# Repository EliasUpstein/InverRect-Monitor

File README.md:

# InverRect-Monitor

**Plataforma Ciberfísica de Simulación, Control HIL y Monitoreo SCADA para Electrónica de Potencia**

---

## 1. Visión y Propósito del Proyecto

**InverRect-Monitor** es una plataforma integral de ingeniería que fusiona la **simulación matemática de alta precisión** con el **control y monitoreo físico en tiempo real** de convertidores estáticos de potencia (rectificadores controlados y no controlados monofásicos y trifásicos, e inversores).

En el estudio y operación de la electrónica de potencia, existe a menudo una desconexión entre:
1. **Los modelos analíticos teóricos:** cálculo de potencias bajo condiciones no senoidales, descomposición en series de Fourier, impacto de armónicas en la red y comportamiento de cargas complejas ($R$, $L$, $C$).
2. **La implementación física de control:** detección precisa del cruce por cero de la red ($50\text{ Hz} / 60\text{ Hz}$), sincronización de microsegundos para el disparo de compuertas (SCR / TRIAC) y aislamiento galvánico de alta tensión.

**InverRect-Monitor** resuelve esta brecha creando un entorno tipo **Hardware-in-the-Loop (HIL) y SCADA**:
* Permite al usuario **analizar, simular y descomponer armónicamente** 12 topologías de convertidores bajo el estándar internacional **IEEE 1459**.
* Permite actuar como **consola SCADA de control remoto**, enviando el ángulo de disparo ($\alpha$) en tiempo real vía **Wi-Fi / UDP** hacia un microcontrolador **ESP32** dedicado al control físico de potencia, garantizando sincronismo estricto e inmunidad a retardos de software.

---

## 2. Arquitectura Global del Sistema Ciberfísico

El sistema opera mediante una división estricta entre la **estación de supervisión de alto nivel (PC)** y el **nodo de control de potencia en tiempo real (ESP32)**:

```
┌─────────────────────────────────────────────────────────────────────────────┐
│                      ESTACIÓN DE SUPERVISIÓN (PC)                           │
│                                                                             │
│   ┌─────────────────────┐   ┌────────────────────────┐   ┌──────────────┐   │
│   │     calculos.py     │◄─►│      interfaz.py       │◄─►│   main.py    │   │
│   │ (NumPy/IEEE 1459/SF)│   │(Tkinter/Matplotlib/UDP)│   │ (Controller) │   │
│   └─────────────────────┘   └───────────┬────────────┘   └──────────────┘   │
└─────────────────────────────────────────┼───────────────────────────────────┘
                                          │ Datagramas UDP ("ALFA:xx.x")
                                          │ Wi-Fi 802.11 (Puerto 8888)
                                          ▼
┌─────────────────────────────────────────────────────────────────────────────┐
│                   NODO DE CONTROL EN TIEMPO REAL (ESP32)                    │
│                                                                             │
│   ┌─────────────────────────────────────┐   ┌───────────────────────────┐   │
│   │               CORE 0                │   │          CORE 1           │   │
│   │   • Tarea FreeRTOS Comunicaciones   │   │   • ISR Cruce por Cero    │   │
│   │   • Servidor UDP & ArduinoOTA       │◄─►│   • Hardware Timer (1 MHz)│   │
│   │   • Sincronización atómica (MUX)    │   │   • Pulso de compuerta    │   │
│   └─────────────────────────────────────┘   └─────────────┬─────────────┘   │
└───────────────────────────────────────────────────────────┼─────────────────┘
                                                            │
                      ┌─────────────────────────────────────┴─────────────┐
                      ▼                                                   ▼
            ┌───────────────────┐                               ┌───────────────────┐
            │  ENTRADA DIGITAL  │                               │  SALIDA DIGITAL   │
            │  GPIO 18 (ZC)     │                               │  GPIO 19 (Gate)   │
            └─────────▲─────────┘                               └─────────┬─────────┘
                      │                                                   │
                      │ Pulso 50 Hz                                       │ Pulso 50 µs
            ┌─────────┴─────────┐                               ┌─────────┴─────────┐
            │ Optoacoplador ZC  │                               │ Driver Opto-TRIAC │
            │      (PC817)      │                               │     (MOC3021)     │
            └─────────▲─────────┘                               └─────────┬─────────┘
                      │                                                   │
     Red Eléctrica ───┴───────────────── Circuito de Potencia ────────────┴──► Carga
     (220V CA / 50 Hz)                   (Tiristores SCR / TRIAC)              (R-L-C)
```

---

## 3. Estructura del Monorepo y Documentación Detallada

El proyecto está organizado de forma modular. Cada subsistema cuenta con su documentación técnica exhaustiva:

```
InverRect-Monitor/
├── pc_software/             # Software de PC: Analizador matemático y panel SCADA
│   ├── calculos.py          # Modelo: Síntesis de ondas, Fourier y cálculo IEEE 1459
│   ├── interfaz.py          # Vista: Interfaz gráfica industrial Tkinter + cliente UDP
│   ├── main.py              # Controlador: Ciclo de vida de la aplicación
│   └── README.md            # 📖 Documentación técnica completa del software de PC
│
├── esp32_firmware/          # Firmwares embebidos para el microcontrolador ESP32 (Arduino IDE)
│   ├── rectificador/        # Sketch del Rectificador Monofásico (ZCD, SCR, ADC, UDP, OTA)
│   │   └── rectificador.ino
│   ├── inversor/            # Sketch modular del Inversor Monofásico (MCPWM 50Hz, Dead-Time, ADC1, UDP, OTA)
│   │   ├── inversor.ino
│   │   ├── config.h
│   │   ├── inverter_mcpwm.h / .cpp
│   │   ├── acquisition.h / .cpp
│   │   └── comms.h / .cpp
│   └── README.md            # 📖 Documentación técnica de hardware, pines, OTA y prueba en osciloscopio
│
├── assets/                  # Diagramas y capturas de pantalla
├── .gitignore               # Filtros de Git para entornos Python y compilaciones C++
└── README.md                # 📖 Visión general del proyecto (este archivo)
```

* 👉 **[Documentación del Software de PC (`pc_software/README.md`)](pc_software/README.md):** Contiene la explicación de los cálculos matemáticos (Fourier, impedancias complejas $R$-$X$, formulación IEEE 1459), descripción de las 12 señales simuladas, guía de la interfaz gráfica y configuración del cliente UDP.
* 👉 **[Documentación del Firmware ESP32 (`esp32_firmware/README.md`)](esp32_firmware/README.md):** Contiene el diagrama de conexionado eléctrico, pinout (GPIO 18 y 19), configuración de FreeRTOS, actualización inalámbrica vía ArduinoOTA y sincronización atómica con spinlocks.

---

## 4. Características Principales

### 🔬 Análisis Matemático y Procesamiento de Señales
* **Correlación Trigonométrica de Fourier (sin FFT):** Cálculo exacto de coeficientes ($a_n, b_n$) mediante integración numérica en el dominio temporal discreto. Evita problemas de *picket-fence* y dispersión espectral (*spectral leakage*) propios de la FFT en señales no periódicas o truncadas.
* **Norma IEEE 1459:** Computa potencia activa ($P$), aparente ($S$), reactiva fundamental ($Q$), distorsión armónica ($D$), factor de potencia ($FP = P/S$) y distorsión armónica total de tensión y corriente ($\text{THD}_V, \text{THD}_I$).
* **Modelado de Impedancias Complejas:** Respuesta dinámica de corriente considerando armónica fundamental y armónicas superiores ($X_n = nX$ para cargas inductivas y $X_n = X/n$ para capacitivas).
* **Biblioteca de 12 Topologías:** Senoidal pura, cuadrada, cuasi-cuadrada, rectificadores monofásicos y trifásicos (media onda y onda completa, controlados y no controlados) y simulación de entrada analógica ADC con ruido gaussiano.

### 🖥️ Interfaz Gráfica SCADA de Alta Legibilidad
* **Diseño Industrial:** Optimizado para pantallas industriales y monitores con escalado DPI (hasta 1080p con 125% DPI scaling).
* **Visualización en Dos Subplots:**
  * Dominio del tiempo: tensión y corriente superpuestas en 2 ciclos con marcación del ángulo $\alpha$.
  * Dominio de la frecuencia: espectro de barras lado a lado de armónicas RMS de tensión y corriente.
* **Cursores Interactivos:** Inspección de valores puntuales al hacer clic sobre cualquier punto de las curvas.
* **Modo en Tiempo Real:** Bucle de simulación y refresco continuo configurable en segundos.

### ⚡ Control de Hardware Físico en Tiempo Real
* **Microsegundos de Precisión:** El ESP32 ejecuta la sincronización de cruce por cero y el temporizador de hardware en el Core 1 con código en `IRAM`, asegurando un disparo libre de jitter. Incorpora un filtro de ventana de supresión de $7000\,\mu\text{s}$ contra transitorios y rebotes en la red de 50 Hz.
* **Enlace Inalámbrico Bidireccional con Handshake (ACK/NACK):** El operador configura la IP en la PC y despacha el comando `"ALFA:xx.x"`. La aplicación verifica activamente la conexión aguardando el paquete de confirmación `"ACK:ALFA:xx.x"` emitido por el ESP32, alertando con precisión si el microcontrolador está apagado o la IP es inalcanzable.
* **Protección de Seguridad Industrial y Monotonicidad:** Compensación continua de retardo de optoacoplador que previene saltos bruscos en bajas conducciones, y validación automática en la interfaz que restringe el ángulo estrictamente al rango seguro $0.0^\circ \le \alpha \le 180.0^\circ$.
* **Flasheo Inalámbrico (OTA):** Soporte para reprogramar el firmware del ESP32 a distancia mientras se encuentra instalado en el banco de pruebas.

---

## 5. Modos de Operación

El sistema puede utilizarse en tres modalidades operativas:

1. **Modo Simulación Pura (Educativo / Diseño):**
   * Se selecciona cualquiera de las topologías de convertidor (índices 0 a 10).
   * Se ajusta la amplitud de tensión, el ángulo de disparo teórico $\alpha$ y los valores de $R$ y $X$.
   * La aplicación reconstruye las ondas analíticas y calcula inmediatamente todos los parámetros de calidad de energía y el espectro armónico.
2. **Modo Hardware-in-the-Loop (HIL) y Control Remoto:**
   * La aplicación de PC se conecta al ESP32 ingresando su dirección IP en la sección de control de hardware.
   * Al modificar $\alpha$ y presionar **"Enviar Ángulo (α) al Hardware"**, el ESP32 actualiza instantáneamente el retardo de compuerta en el circuito de tiristores real.
   * Permite contrastar la respuesta teórica calculada en la PC contra las mediciones en osciloscopio tomadas sobre el convertidor físico.
3. **Modo Instrumentación / Telemetría ADC:**
   * Seleccionando la señal `11. Muestras ADC (Simuladas)`, el sistema evalúa señales analógicas adquiridas con componentes estocásticos de ruido.
   * Permite continuar despachando órdenes de hardware al ESP32 manteniendo independiente el análisis de la señal capturada.

---

## 6. Puesta en Marcha Rápida (Quickstart)

### Paso 1: Clonar el Repositorio
```bash
git clone https://github.com/EliasUpstein/InverRect-Monitor.git
cd InverRect-Monitor
```

### Paso 2: Configurar el Entorno Python
```bash
# Crear entorno virtual
python -m venv venv

# Activar entorno virtual
# En Windows:
venv\Scripts\activate
# En Linux/macOS:
source venv/bin/activate

# Instalar dependencias
pip install numpy matplotlib
```

### Paso 3: Ejecutar la Interfaz de PC
```bash
python pc_software/main.py
```

### Paso 4 (Opcional): Cargar el Firmware al ESP32
1. Abrir `esp32_firmware/rectificador/rectificador.ino` o `esp32_firmware/inversor/inversor.ino` en Arduino IDE (o PlatformIO).
2. Configurar `WIFI_SSID` y `WIFI_PASSWORD` en el sketch (para el inversor, en `esp32_firmware/inversor/config.h`).
3. Flashear el microcontrolador por primera vez vía USB y observar la IP en el Monitor Serie (115200 bps). Las siguientes actualizaciones pueden realizarse por **ArduinoOTA** (`esp32-rmmoc` o `esp32-inversor`).
4. Seleccionar el dispositivo (`Rectificador` o `Inversor`) e ingresar la IP en la interfaz gráfica de PC.

---

## 7. Referencias Normativas y Bibliográficas
* **IEEE Std 1459-2010:** *IEEE Standard Definitions for the Measurement of Electric Power Quantities Under Sinusoidal, Nonsinusoidal, Balanced, or Unbalanced Conditions*.
* **Mohan, Undeland, Robbins:** *Power Electronics: Converters, Applications, and Design*, John Wiley & Sons.
* **Rashid, Muhammad H.:** *Power Electronics Handbook*, Academic Press.
* **Espressif Systems:** *ESP32 Technical Reference Manual & FreeRTOS Architecture*.

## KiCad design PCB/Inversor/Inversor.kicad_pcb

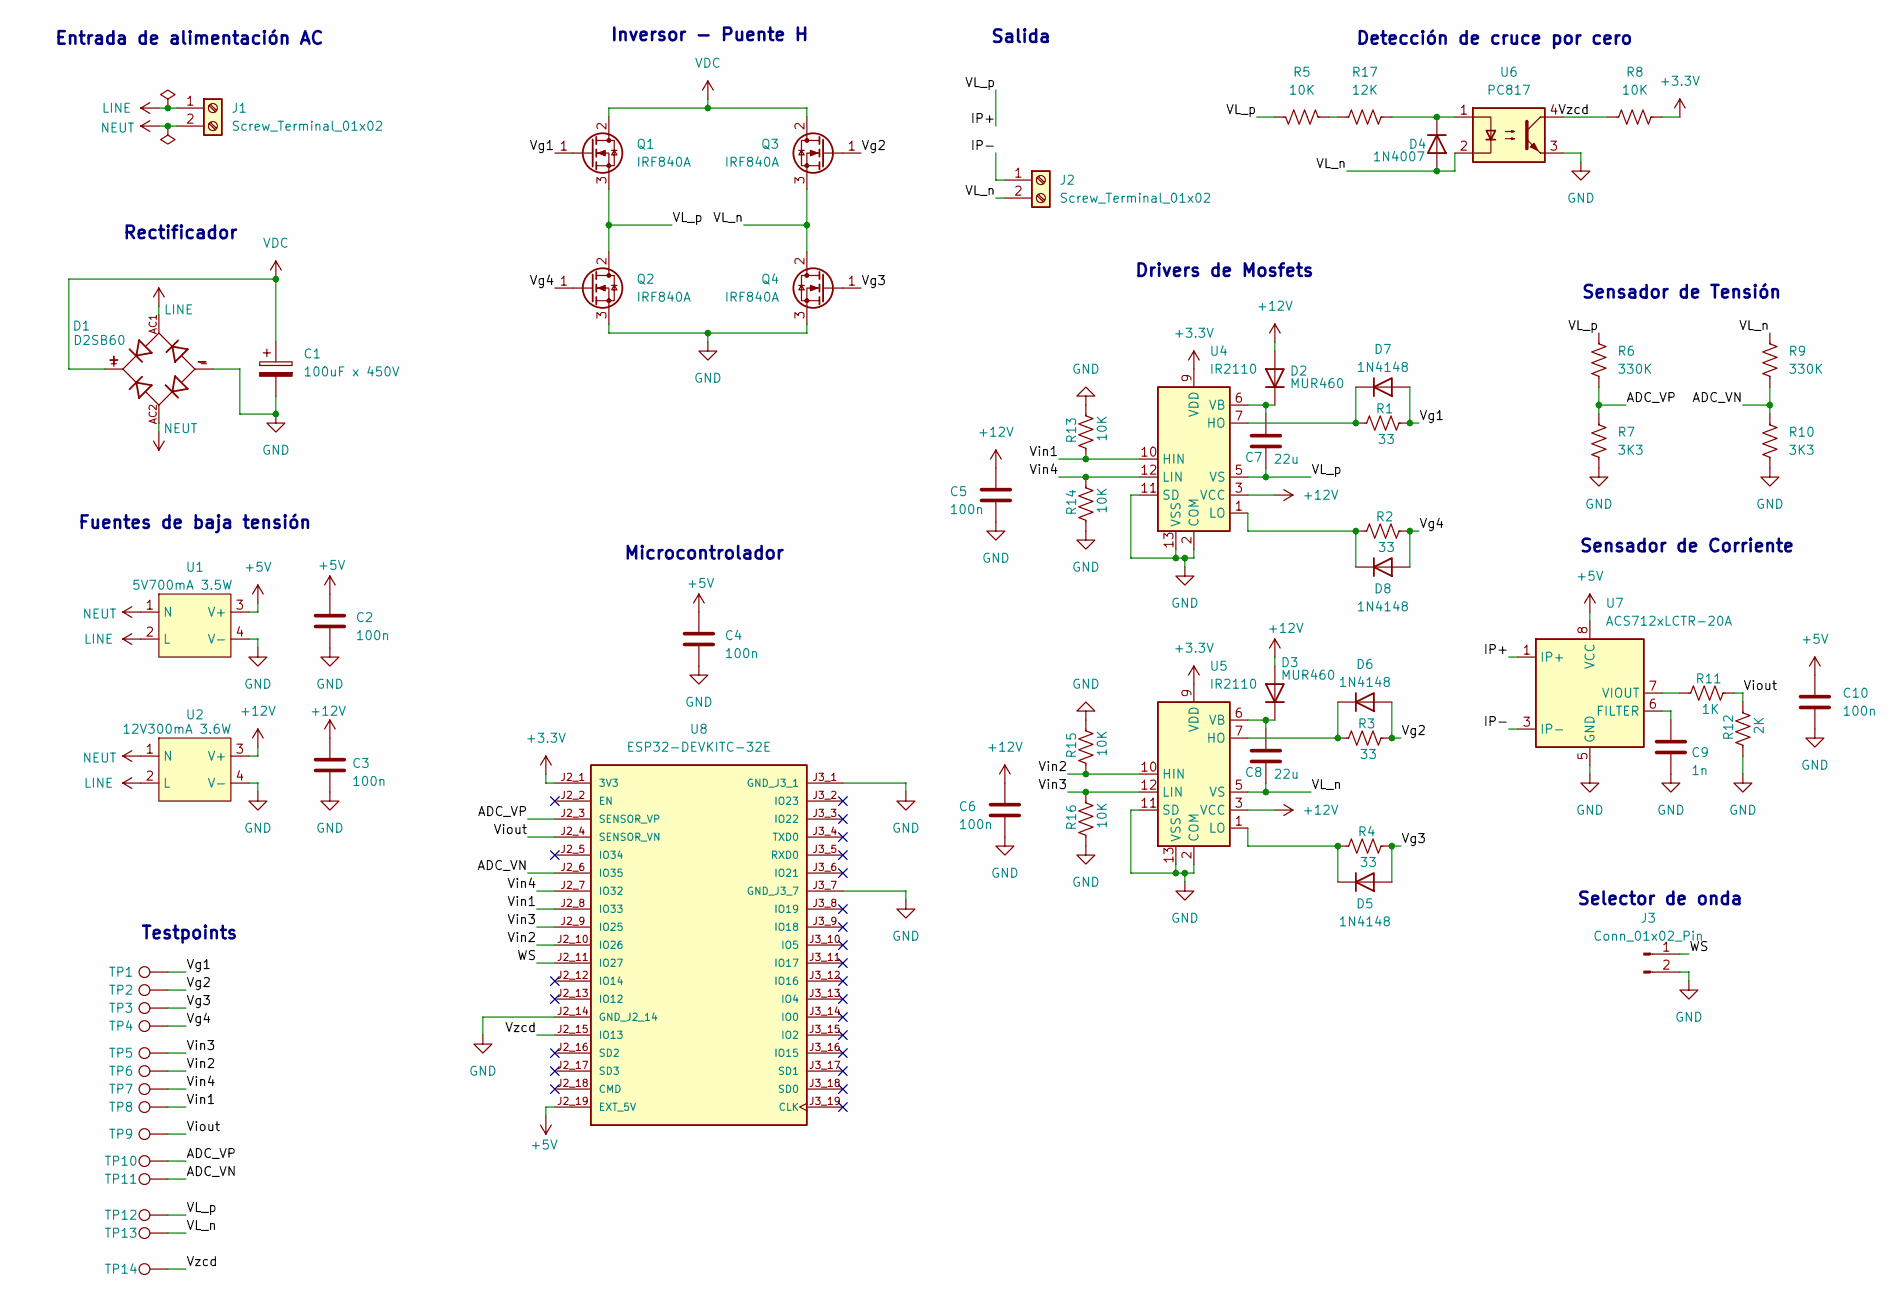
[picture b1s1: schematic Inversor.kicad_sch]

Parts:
C1: 100uF x 450V; CP_Radial_D18.0mm_P7.50mm
C2, C3, C4, C5, C6, C10: 100n; C_Disc_D4.3mm_W1.9mm_P5.00mm
C7: 22u; CP_Radial_D5.0mm_P2.00mm
C8: 22u; CP_Radial_D4.0mm_P2.00mm
C9: 1n; C_Disc_D4.3mm_W1.9mm_P5.00mm
D1: D2SB60; SIP350W100P500L2000H1400Q4; MPN D2SB60
D2, D3: MUR460; D_DO-41_SOD81_P10.16mm_Horizontal
D4: 1N4007; D_DO-41_SOD81_P10.16mm_Horizontal
D5, D6, D7, D8: 1N4148; D_DO-35_SOD27_P7.62mm_Horizontal
J1, J2: Screw_Terminal_01x02; TerminalBlock_Phoenix_MKDS-1,5-2-5.08_1x02_P5.08mm_Horizont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
J3: Conn_01x02_Pin; PinHeader_2x01_P2.54mm_Vertical
Q1, Q2, Q3, Q4: IRF840A; TO-220-3_Vertical
R1, R2, R3, R4: 33; R_Axial_DIN0309_L9.0mm_D3.2mm_P15.24mm_Horizontal
R5: 10K; R_Axial_DIN0414_L11.9mm_D4.5mm_P25.40mm_Horizontal
R6, R9: 330K; R_Axial_DIN0309_L9.0mm_D3.2mm_P15.24mm_Horizontal
R7, R10: 3K3; R_Axial_DIN0309_L9.0mm_D3.2mm_P15.24mm_Horizontal
R8, R13, R14, R15, R16: 10K; R_Axial_DIN0309_L9.0mm_D3.2mm_P15.24mm_Horizontal
R11: 1K; R_Axial_DIN0309_L9.0mm_D3.2mm_P15.24mm_Horizontal
R12: 2K; R_Axial_DIN0309_L9.0mm_D3.2mm_P15.24mm_Horizontal
R17: 12K; R_Axial_DIN0414_L11.9mm_D4.5mm_P25.40mm_Horizontal
TP1, TP2, TP3, TP4, TP5, TP6, TP7, TP8, TP9, TP10, TP11, TP12, TP13, TP14: TestPoint; PinHeader_1x01_P2.54mm_Vertical
U1: 5V700mA 3.5W; WX-DC12003
U2: 12V300mA 3.6W; WX-DC12003
U4, U5: IR2110; DIP-14_W7.62mm
U6: PC817; DIP-4_W7.62mm
U7: ACS712xLCTR-20A; SOIC-8_3.9x4.9mm_P1.27mm
U8: ESP32-DEVKITC-32E; MODULE_ESP32-DEVKITC-32E; MPN ESP32-DEVKITC-32E

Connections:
+3.3V: R8.2, U4.9 (VDD), U5.9 (VDD), U8.J2_1 (3V3)
+5V: C2.1, C4.1, C10.1, U1.3 (V+), U7.8 (VCC), U8.J2_19 (EXT_5V)
+12V: C3.1, C5.1, C6.1, D2.2 (A), D3.2 (A), U2.3 (V+), U4.3 (VCC), U5.3 (VCC)
/ADC_VN: R9.2, R10.1, TP11.1 (1_1), U8.J2_6 (IO35)
/ADC_VP: R6.2, R7.1, TP10.1 (1_1), U8.J2_3 (SENSOR_VP)
/IP+: C7.2, Q1.3 (S), Q2.2 (D), R5.2, R6.1, TP12.1 (1_1), U4.5 (VS), U7.1 (IP+), U7.2 (IP+)
/IP-: J2.1, U7.3 (IP-), U7.4 (IP-)
/VL_n: C8.2, D4.2 (A), J2.2, Q3.3 (S), Q4.2 (D), R9.1, TP13.1 (1_1), U5.5 (VS), U6.2
/Vg1: D7.2 (A), Q1.1 (G), R1.2, TP1.1 (1_1)
/Vg2: D6.2 (A), Q3.1 (G), R3.2, TP2.1 (1_1)
/Vg3: D5.2 (A), Q4.1 (G), R4.2, TP3.1 (1_1)
/Vg4: D8.2 (A), Q2.1 (G), R2.2, TP4.1 (1_1)
/Vin1: R13.1, TP8.1 (1_1), U4.10 (HIN), U8.J2_8 (IO33)
/Vin2: R15.1, TP6.1 (1_1), U5.10 (HIN), U8.J2_10 (IO26)
/Vin3: R16.2, TP5.1 (1_1), U5.12 (LIN), U8.J2_9 (IO25)
/Vin4: R14.2, TP7.1 (1_1), U4.12 (LIN), U8.J2_7 (IO32)
/Viout: R11.2, R12.2, TP9.1 (1_1), U8.J2_4 (SENSOR_VN)
/Vzcd: R8.1, TP14.1 (1_1), U6.4, U8.J2_15 (IO13)
/WS: J3.1, U8.J2_11 (IO27)
GND: C1.2, C2.2, C3.2, C4.2, C5.2, C6.2, C9.2, C10.2, D1.-, J3.2, Q2.3 (S), Q4.3 (S), R7.2, R10.2, R12.1, R13.2, R14.1, R15.2, R16.1, U1.4 (V-), U2.4 (V-), U4.2 (COM), U4.11 (SD), U4.13 (VSS), U5.2 (COM), U5.11 (SD), U5.13 (VSS), U6.3, U7.5 (GND), U8.J2_14 (GND_J2_14), U8.J3_1 (GND_J3_1), U8.J3_7 (GND_J3_7)
LINE: D1.AC1, J1.1, U1.2 (L), U2.2 (L)
NEUT: D1.AC2, J1.2, U1.1 (N), U2.1 (N)
unnamed: C7.1, D2.1 (K), U4.6 (VB)
unnamed: C8.1, D3.1 (K), U5.6 (VB)
unnamed: D4.1 (K), R17.2, U6.1
unnamed: D5.1 (K), R4.1, U5.1 (LO)
unnamed: D6.1 (K), R3.1, U5.7 (HO)
unnamed: D7.1 (K), R1.1, U4.7 (HO)
unnamed: D8.1 (K), R2.1, U4.1 (LO)
unnamed: R5.1, R17.1
unnamed: C9.1, U7.6 (FILTER)
unnamed: R11.1, U7.7 (VIOUT)
VDC: C1.1, D1.+, Q1.2 (D), Q3.2 (D)

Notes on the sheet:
Inversor - Puente H
Fuentes de baja tensión
Testpoints
Rectificador
Sensador de Tensión
Microcontrolador
Detección de cruce por cero
Entrada de alimentación AC
Selector de onda
Sensador de Corriente
Drivers de Mosfets
Salida

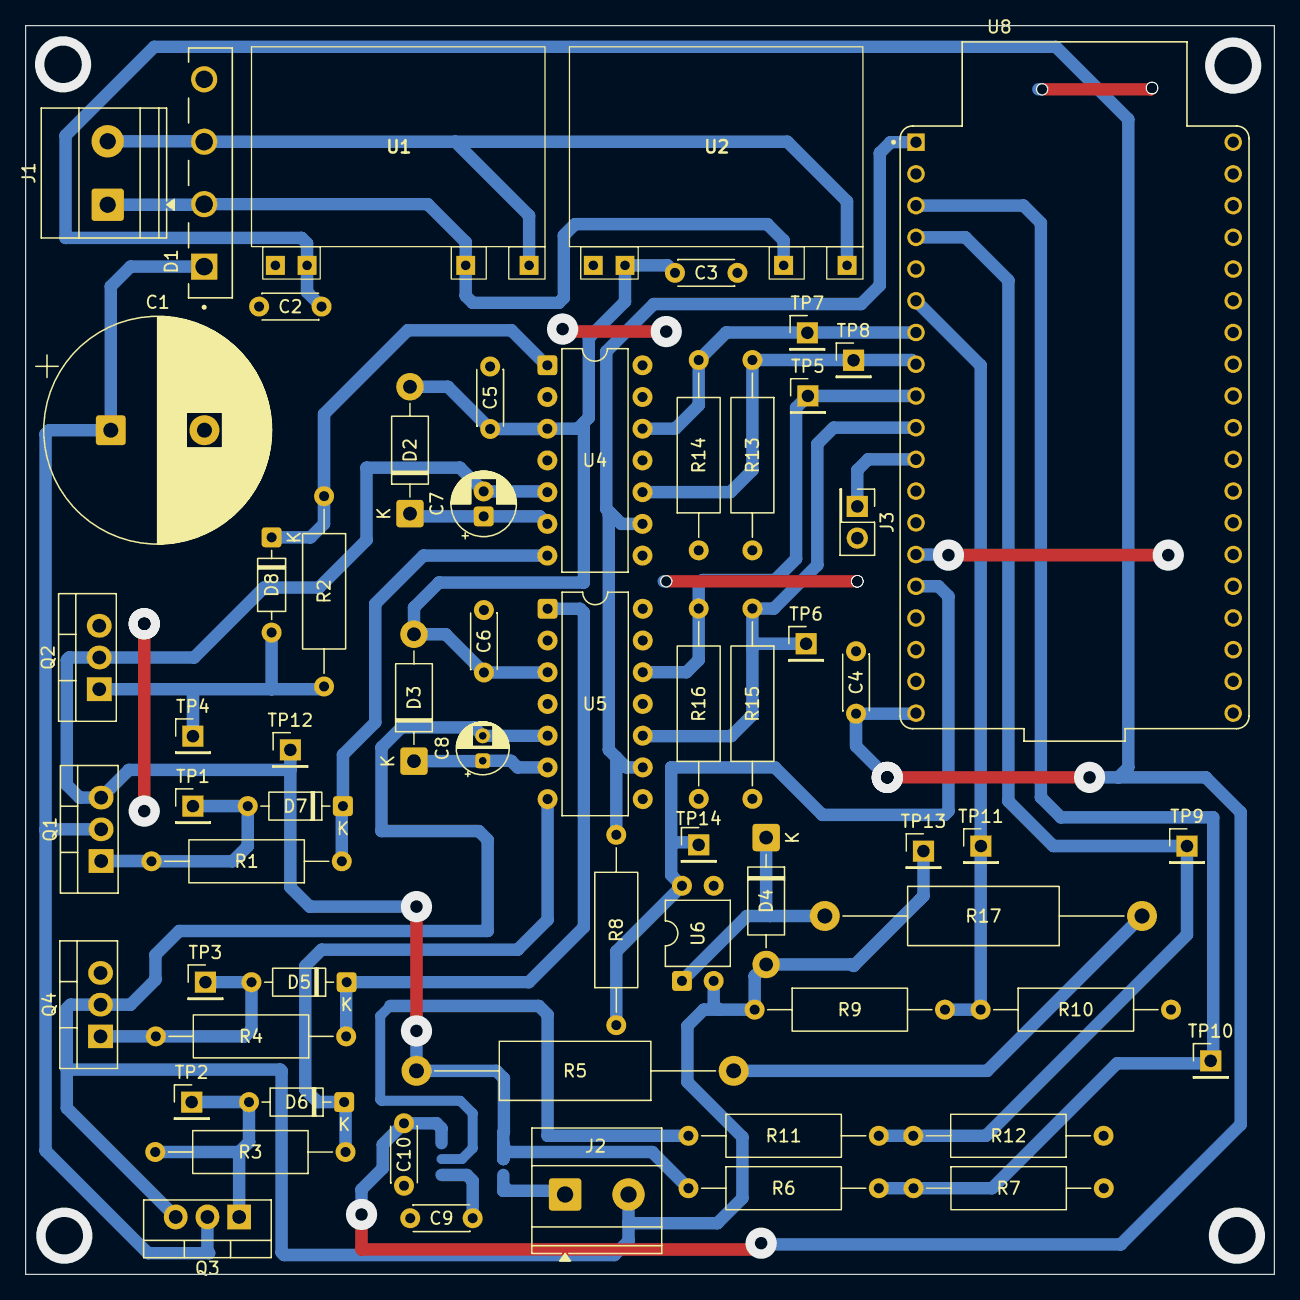
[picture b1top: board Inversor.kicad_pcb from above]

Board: 2 copper layers, 100.0 x 100.0 mm, 63 parts (1 on the bottom side), 33 nets.

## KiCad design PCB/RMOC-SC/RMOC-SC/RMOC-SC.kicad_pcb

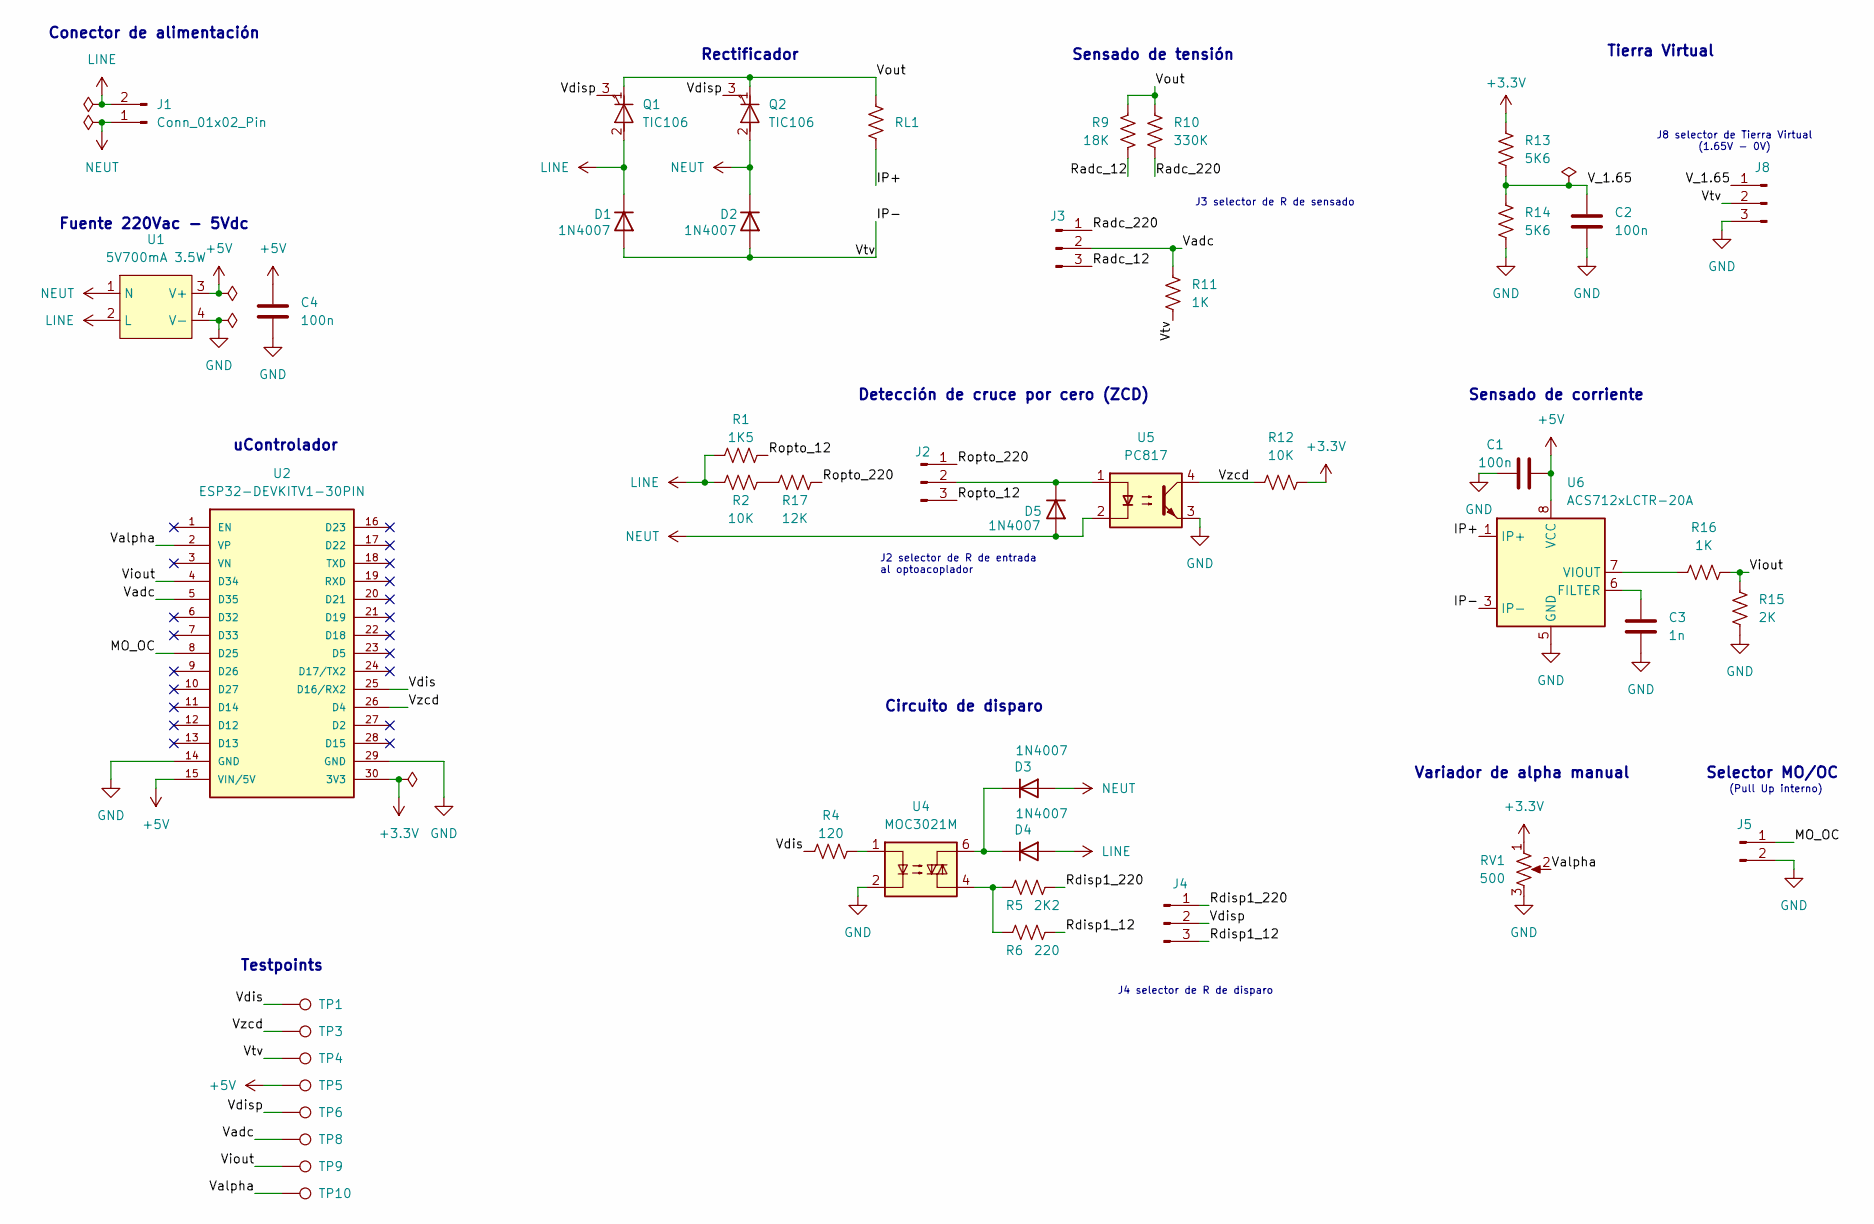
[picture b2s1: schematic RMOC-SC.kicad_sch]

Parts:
C1, C2, C4: 100n; C_Disc_D5.0mm_W2.5mm_P5.00mm
C3: 1n; C_Disc_D5.0mm_W2.5mm_P5.00mm
D1, D2, D3, D4, D5: 1N4007; D_DO-41_SOD81_P10.16mm_Horizontal
J1: Conn_01x02_Pin; Conn_220_tipo8
J2, J3, J4, J8: Conn_01x03_Pin; PinHeader_1x03_P2.54mm_Vertical
J5: Conn_01x02_Pin; PinHeader_1x02_P2.54mm_Vertical
Q1, Q2: TIC106; TO-220-3_Vertical
R1: 1K5; R_Axial_DIN0309_L9.0mm_D3.2mm_P12.70mm_Horizontal
R2: 10K; R_Axial_DIN0614_L14.3mm_D5.7mm_P20.32mm_Horizontal
R4: 120; R_Axial_DIN0309_L9.0mm_D3.2mm_P12.70mm_Horizontal
R5: 2K2; R_Axial_DIN0309_L9.0mm_D3.2mm_P12.70mm_Horizontal
R6: 220; R_Axial_DIN0309_L9.0mm_D3.2mm_P12.70mm_Horizontal
R9: 18K; R_Axial_DIN0309_L9.0mm_D3.2mm_P12.70mm_Horizontal
R10: 330K; R_Axial_DIN0309_L9.0mm_D3.2mm_P12.70mm_Horizontal
R11, R16: 1K; R_Axial_DIN0309_L9.0mm_D3.2mm_P12.70mm_Horizontal
R12: 10K; R_Axial_DIN0309_L9.0mm_D3.2mm_P12.70mm_Horizontal
R13, R14: 5K6; R_Axial_DIN0309_L9.0mm_D3.2mm_P12.70mm_Horizontal
R15: 2K; R_Axial_DIN0309_L9.0mm_D3.2mm_P12.70mm_Horizontal
R17: 12K; R_Axial_DIN0614_L14.3mm_D5.7mm_P20.32mm_Horizontal
RL1: R_US; Altech_AK100_1x02_P5.00mm
RV1: 500; Potentiometer_Piher_PC-16_Single_Horizontal
TP1, TP3, TP4, TP5, TP6, TP8, TP9, TP10: TestPoint; PinHeader_1x01_P2.54mm_Vertical
U1: 5V700mA 3.5W; WX-DC12003
U2: ESP32-DEVKITV1-30PIN; ESP32-DEVKIT-30PIN; PARTREV V4
U4: MOC3021M; DIP-6_W7.62mm_LongPads
U5: PC817; DIP-4_W7.62mm
U6: ACS712xLCTR-20A; SOIC-8_3.9x4.9mm_P1.27mm

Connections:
+3.3V: R12.2, R13.1, RV1.1, U2.30 (3V3)
+5V: C1.2, C4.1, TP5.1 (1_1), U1.3 (V+), U2.15 (VIN/5V), U6.8 (VCC)
/IP+: RL1.2, U6.1 (IP+), U6.2 (IP+)
/IP-: D1.2 (A), D2.2 (A), J8.2, R11.2, TP4.1 (1_1), U6.3 (IP-), U6.4 (IP-)
/MO_OC: J5.1, U2.8 (D25)
/Radc_12: J3.3, R9.2
/Radc_220: J3.1, R10.2
/Rdisp1_12: J4.3, R6.2
/Rdisp1_220: J4.1, R5.2
/Ropto_12: J2.3, R1.2
/Ropto_220: J2.1, R17.2
/V_1.65: C2.1, J8.1, R13.2, R14.1
/Vadc: J3.2, R11.1, TP8.1 (1_1), U2.5 (D35)
/Valpha: RV1.2, TP10.1 (1_1), U2.2 (VP)
/Vdis: R4.1, TP1.1 (1_1), U2.25 (D16/RX2)
/Vdisp: J4.2, Q1.3 (G), Q2.3 (G), TP6.1 (1_1)
/Viout: R15.1, R16.2, TP9.1 (1_1), U2.4 (D34)
/Vout: Q1.1 (K), Q2.1 (K), R9.1, R10.1, RL1.1
/Vzcd: R12.1, TP3.1 (1_1), U2.26 (D4), U5.4
GND: C1.1, C2.2, C3.2, C4.2, J5.2, J8.3, R14.2, R15.2, RV1.3, U1.4 (V-), U2.14 (GND), U2.29 (GND), U4.2, U5.3, U6.5 (GND)
LINE: D1.1 (K), D4.2 (A), J1.2, Q1.2 (A), R1.1, R2.1, U1.2 (L)
NEUT: D2.1 (K), D3.2 (A), D5.2 (A), J1.1, Q2.2 (A), U1.1 (N), U5.2
unnamed: D3.1 (K), D4.1 (K), U4.6
unnamed: D5.1 (K), J2.2, U5.1
unnamed: R4.2, U4.1
unnamed: R5.1, R6.1, U4.4
unnamed: R2.2, R17.1
unnamed: C3.1, U6.6 (FILTER)
unnamed: R16.1, U6.7 (VIOUT)

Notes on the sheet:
Rectificador
Detección de cruce por cero (ZCD)
Sensado de corriente
Variador de alpha manual
J8 selector de Tierra Virtual (1.65V - 0V)
Testpoints
Fuente 220Vac - 5Vdc
J2 selector de R de entrada al optoacoplador
Selector MO/OC
uControlador
Circuito de disparo
(Pull Up interno)
J4 selector de R de disparo
Sensado de tensión
J3 selector de R de sensado
Tierra Virtual
Conector de alimentación

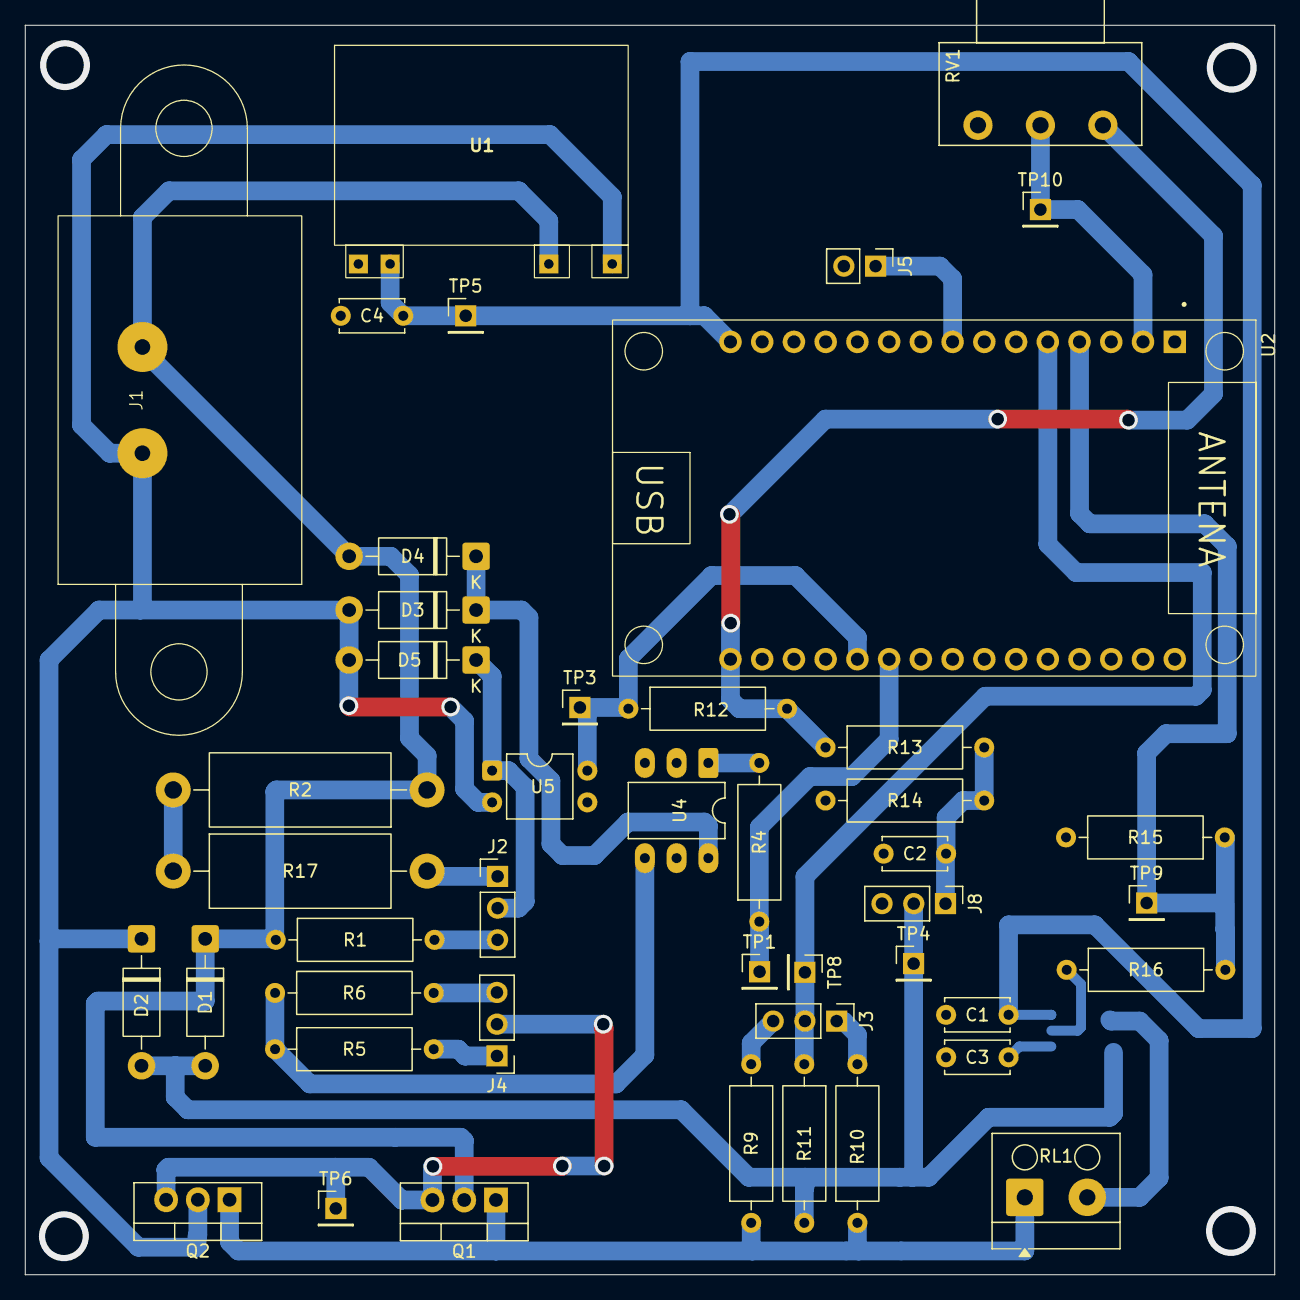
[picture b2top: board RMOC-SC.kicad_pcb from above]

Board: 2 copper layers, 100.0 x 100.0 mm, 46 parts (1 on the bottom side), 29 nets.

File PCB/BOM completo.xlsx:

Reference | Qty | Value | Footprint
C1,C2,C4 | 3 | 100n | Capacitor_THT:C_Disc_D5.0mm_W2.5mm_P5.00mm
C3 | 1 | 1n | Capacitor_THT:C_Disc_D5.0mm_W2.5mm_P5.00mm
D1,D2,D3,D4,D5 | 5 | 1N4007 | Diode_THT:D_DO-41_SOD81_P10.16mm_Horizontal
J1 | 1 | Conn_01x02_Pin | WX-DC12003:Conn_220_tipo8
J2,J3,J4,J8 | 4 | Conn_01x03_Pin | Connector_PinHeader_2.54mm:PinHeader_1x03_P2.54mm_Vertical
J5 | 1 | Conn_01x02_Pin | Connector_PinHeader_2.54mm:PinHeader_1x02_P2.54mm_Vertical
Q1,Q2 | 2 | TIC106 | Package_TO_SOT_THT:TO-220-3_Vertical
R1 | 1 | 1K5 | Resistor_THT:R_Axial_DIN0309_L9.0mm_D3.2mm_P12.70mm_Horizontal
R2 | 1 | 10K | Resistor_THT:R_Axial_DIN0614_L14.3mm_D5.7mm_P20.32mm_Horizontal
R4 | 1 | 120 | Resistor_THT:R_Axial_DIN0309_L9.0mm_D3.2mm_P12.70mm_Horizontal
R5 | 1 | 2K2 | Resistor_THT:R_Axial_DIN0309_L9.0mm_D3.2mm_P12.70mm_Horizontal
R6 | 1 | 220 | Resistor_THT:R_Axial_DIN0309_L9.0mm_D3.2mm_P12.70mm_Horizontal
R9 | 1 | 18K | Resistor_THT:R_Axial_DIN0309_L9.0mm_D3.2mm_P12.70mm_Horizontal
R10 | 1 | 330K | Resistor_THT:R_Axial_DIN0309_L9.0mm_D3.2mm_P12.70mm_Horizontal
R11,R16 | 2 | 1K | Resistor_THT:R_Axial_DIN0309_L9.0mm_D3.2mm_P12.70mm_Horizontal
R12 | 1 | 10K | Resistor_THT:R_Axial_DIN0309_L9.0mm_D3.2mm_P12.70mm_Horizontal
R13,R14 | 2 | 5K6 | Resistor_THT:R_Axial_DIN0309_L9.0mm_D3.2mm_P12.70mm_Horizontal
R15 | 1 | 2K | Resistor_THT:R_Axial_DIN0309_L9.0mm_D3.2mm_P12.70mm_Horizontal
R17 | 1 | 12K | Resistor_THT:R_Axial_DIN0614_L14.3mm_D5.7mm_P20.32mm_Horizontal
RL1 | 1 | R_US | TerminalBlock_Altech:Altech_AK100_1x02_P5.00mm
RV1 | 1 | 500 | Potentiometer_THT:Potentiometer_Piher_PC-16_Single_Horizontal
TP1,TP3,TP4,TP5,TP6,TP8,TP9,TP10 | 8 | TestPoint | Connector_PinHeader_2.54mm:PinHeader_1x01_P2.54mm_Vertical
U1 | 1 | 5V700mA 3.5W | WX-DC12003:WX-DC12003
U2 | 1 | ESP32-DEVKITV1-30PIN | ESP32-DEVKITV1-30PIN:ESP32-DEVKIT-30PIN
U4 | 1 | MOC3021M | Package_DIP:DIP-6_W7.62mm_LongPads
U5 | 1 | PC817 | Package_DIP:DIP-4_W7.62mm
U6 | 1 | ACS712xLCTR-20A | Package_SO:SOIC-8_3.9x4.9mm_P1.27mm

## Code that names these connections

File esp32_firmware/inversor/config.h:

#pragma once

#include <Arduino.h>
#include <stdint.h>

/**
 * ============================================================================
 * Proyecto: InverRect-Monitor - Firmware del Inversor Monofásico (50 Hz)
 * Archivo:  esp32_firmware/inversor/config.h
 * Hardware: PCB/Inversor/Inversor.kicad_pcb (ESP32-DEVKITC-32E + 2x IR2110 + 4x IRF840A)
 *
 * Definición centralizada de pines (verificados contra el PCB de KiCad),
 * parámetros de seguridad anti shoot-through, escalado analógico ADC1 y red.
 * ============================================================================
 */

// ============================================================================
// 1. ASIGNACIÓN DE PINES DE HARDWARE (Verificados en PCB/Inversor/Inversor.kicad_pcb)
// ============================================================================

// Pierna P (U4: IR2110 -> nodo /IP+ -> Q1 superior, Q2 inferior)
// Ambos pines cuentan con pull-down externo de 10 kOhm (R13, R14) en el PCB.
constexpr int PIN_VIN1_P_HIN = 33;  // U8 IO33 -> U4 HIN (pin 10) -> /Vg1 -> Q1 (High-Side P)
constexpr int PIN_VIN4_P_LIN = 32;  // U8 IO32 -> U4 LIN (pin 12) -> /Vg4 -> Q2 (Low-Side P)

// Pierna N (U5: IR2110 -> nodo /VL_n -> Q3 superior, Q4 inferior)
// Ambos pines cuentan con pull-down externo de 10 kOhm (R15, R16) en el PCB.
constexpr int PIN_VIN2_N_HIN = 26;  // U8 IO26 -> U5 HIN (pin 10) -> /Vg2 -> Q3 (High-Side N)
constexpr int PIN_VIN3_N_LIN = 25;  // U8 IO25 -> U5 LIN (pin 12) -> /Vg3 -> Q4 (Low-Side N)

// Selector físico de forma de onda (Jumper J3 entre IO27 y GND)
// HIGH (abierto) = Onda Cuadrada (alpha = 0°)
// LOW  (cerrado) = Onda Cuasicuadrada (alpha = 30°)
constexpr int PIN_WAVE_SELECTOR = 27; // U8 IO27 -> /WS (configurar INPUT_PULLUP)

// Sensado Analógico (ESTRICTAMENTE en ADC1 para compatibilidad total con Wi-Fi)
constexpr int PIN_ADC_VP    = 36;   // U8 SENSOR_VP (ADC1_CH0) -> /ADC_VP (R6=330k / R7=3.3k en /IP+)
constexpr int PIN_ADC_VN    = 35;   // U8 IO35      (ADC1_CH7) -> /ADC_VN (R9=330k / R10=3.3k en /VL_n)
constexpr int PIN_ADC_VIOUT = 39;   // U8 SENSOR_VN (ADC1_CH3) -> /Viout  (ACS712-20A + R11=1k / R12=2k)

// Detector óptico de polaridad de salida (U6: PC817 con pull-up R8=10k a 3.3V)
// LOW cuando V_out > 0 (+VDC en /IP+ respecto a /VL_n), HIGH cuando V_out <= 0.
constexpr int PIN_VZCD = 13;        // U8 IO13 -> /Vzcd (diagnóstico / verificación de salida)

// ============================================================================
// 2. PARÁMETROS DEL INVERSOR, MCPWM Y SEGURIDAD (ANTI SHOOT-THROUGH)
// ============================================================================
#define INVERTER_FREQ_HZ            50.0f
#define MCPWM_RESOLUTION_HZ         1000000UL   // 1 MHz (1 tick = 1 us)
#define MCPWM_PERIOD_TICKS          20000UL     // 20 000 us = 20.000 ms (50.000 Hz)
#define MCPWM_HALF_PERIOD_TICKS     10000UL     // 10 000 us = 180°

// Tiempo muerto por hardware (RED y FED) en microsegundos
#define DEAD_TIME_US                50U
#define DEAD_TIME_MIN_SAFE_US       10U
#define DEAD_TIME_MAX_SAFE_US       500U

// Margen base desde t=0 (TEZ) para evitar que ningún comparador colisione con 0 o 20000
#define MCPWM_BASE_OFFSET_TICKS     600UL

// Verificaciones obligatorias en tiempo de compilación
static_assert(DEAD_TIME_US >= DEAD_TIME_MIN_SAFE_US,
              "SEGURIDAD CRITICA: DEAD_TIME_US debe ser >= 10 us para evitar shoot-through.");
static_assert(DEAD_TIME_US <= DEAD_TIME_MAX_SAFE_US,
              "DEAD_TIME_US excede el maximo permitido (500 us) para 50 Hz.");
static_assert(MCPWM_BASE_OFFSET_TICKS > DEAD_TIME_US,
              "MCPWM_BASE_OFFSET_TICKS debe ser estrictamente mayor que DEAD_TIME_US.");

// Pre-carga de capacitores de bootstrap (C7 y C8 = 22 uF con MUR460 desde +12V)
constexpr uint32_t BOOTSTRAP_PRECHARGE_MS = 5;

// Límites seguros del ángulo de muesca alpha (Phase-Shift Control: conducción = 180° - 2*alpha)
constexpr float ALPHA_MIN_DEG           = 0.0f;   // Onda cuadrada pura (180° de conducción)
constexpr float ALPHA_QUASI_DEFAULT_DEG = 30.0f;  // Onda cuasicuadrada óptima (120°, elimina 3er armónico)
constexpr float ALPHA_MAX_DEG           = 60.0f;  // Mínimo pulso seguro de 60° (conducción 3.33 ms)

// Antirrebote por software del jumper físico WS
constexpr uint32_t WS_DEBOUNCE_MS = 50;

// ============================================================================
// 3. PARÁMETROS DE ADQUISICIÓN Y ESCALADO ADC1 (SIN CÁLCULOS ESTADÍSTICOS EN ESP32)
// ============================================================================
constexpr int NUM_MUESTRAS_CICLO = 64; // 64 muestras / 20 ms = 3200 Hz (compatible con GUI y 1 datagrama UDP)

// Divisores resistivos de tensión diferencial en Pierna P (/IP+) y Pierna N (/VL_n)
// R6 = R9 = 330 kOhm, R7 = R10 = 3.3 kOhm -> Factor = (330k + 3.3k) / 3.3k = 101.0
constexpr float R_DIV_V_SUP_OHM    = 330000.0f;
constexpr float R_DIV_V_INF_OHM    = 3300.0f;
constexpr float FACTOR_ESCALA_V    = (R_DIV_V_SUP_OHM + R_DIV_V_INF_OHM) / R_DIV_V_INF_OHM; // 101.0

// Sensor de corriente ACS712-20A + divisor resistivo R11=1 kOhm (serie) / R12=2 kOhm (a GND)
// Ganancia del divisor = 2/3 -> factor inverso = 1.5
// Offset nominal en pin: 2.50 V * (2/3) = 1.6667 V | Sensibilidad en pin: 66.67 mV/A
constexpr float R_DIV_ACS_SERIE_OHM      = 1000.0f;
constexpr float R_DIV_ACS_GND_OHM        = 2000.0f;
constexpr float FACTOR_DIVISOR_ACS       = (R_DIV_ACS_SERIE_OHM + R_DIV_ACS_GND_OHM) / R_DIV_ACS_GND_OHM; // 1.5
constexpr float ACS712_OFFSET_NOMINAL_V  = 2.50f;
constexpr float ACS712_OFFSET_PIN_NOM_V  = ACS712_OFFSET_NOMINAL_V / FACTOR_DIVISOR_ACS; // ~1.6667 V
constexpr float ACS712_SENSIBILIDAD_V_A  = 0.100f; // 100 mV/A para ACS712xLCTR-20A
constexpr int   ACS712_CAL_MUESTRAS      = 128;    // Muestras promediadas con puente OFF en Safe-Boot

// Ventana de validez del offset calibrado del ACS712 en pin (evita calibración errónea si no hay +5V)
constexpr float ACS712_PIN_CAL_MIN_V = 1.20f;
constexpr float ACS712_PIN_CAL_MAX_V = 2.10f;

// ============================================================================
// 4. CONFIGURACIÓN DE RED WI-FI, UDP SCADA Y ARDUINO OTA (CORE 0)
// ============================================================================
#define WIFI_SSID           "Galaxy A71"      // Configurar con el SSID de la red local
#define WIFI_PASSWORD       "elias3503"  // Configurar con la clave de la red local
#define UDP_PORT            8888                // Puerto UDP compatible con pc_software/interfaz.py
#define OTA_HOSTNAME        "esp32-inversor"    // Hostname exclusivo para OTA (distinto de esp32-rmmoc)
#define OTA_PASSWORD        "epstein"           // Contraseña OTA del proyecto

// ============================================================================
// 5. ESTADO COMPARTIDO ENTRE CORE 0 (RED/OTA) Y CORE 1 (MCPWM/ADC/WS)
// ============================================================================
enum InverterWaveMode : uint8_t {
    WAVE_SQUARE = 0,       // Onda Cuadrada (alpha = 0°)
    WAVE_QUASI_SQUARE = 1  // Onda Cuasicuadrada (alpha configurable, 30° por defecto)
};

struct InverterState {
    bool running;                  // true = MCPWM conmutando; false = Parada de emergencia (all LOW)
    bool estop_latched;            // true = Parada de emergencia activa (requiere START explícito)
    bool control_interfaz_activo;  // true = Obedece comandos UDP; false = Obedece jumper físico WS
    bool jumper_ws_closed;         // true = Jumper WS a GND (Cuasicuadrada); false = Abierto (Cuadrada)
    InverterWaveMode wave_mode;    // Modo de onda activo
    float alpha_deg;               // Ángulo alpha efectivo (0.0° a 60.0°)
};

// Spinlock compartido para lectura/escritura atómica del estado y doble buffer ADC
extern portMUX_TYPE g_stateMux;
extern volatile InverterState g_inverterState;

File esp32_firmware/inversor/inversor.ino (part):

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    // 5. Iniciar tarea de comunicaciones (Wi-Fi + UDP puerto 8888 + ArduinoOTA) en Core 0
    commsStartTaskOnCore0();

    Serial.println("[Core 1] Pines activos -> Pierna P: Vin1=IO33, Vin4=IO32 | Pierna N: Vin2=IO26, Vin3=IO25");
    Serial.println("[Core 1] ADC1 -> ADC_VP=IO36, ADC_VN=IO35, Viout=IO39 | WS=IO27");
    Serial.println("[Serial] Comandos disponibles: CUADRADA | CUASI | <0..60> | HW | STOP | START | STATUS");
}
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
